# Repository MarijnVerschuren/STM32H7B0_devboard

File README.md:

# STM32H7B0_devboard
devboard featuring the STM32H7B0VBT6

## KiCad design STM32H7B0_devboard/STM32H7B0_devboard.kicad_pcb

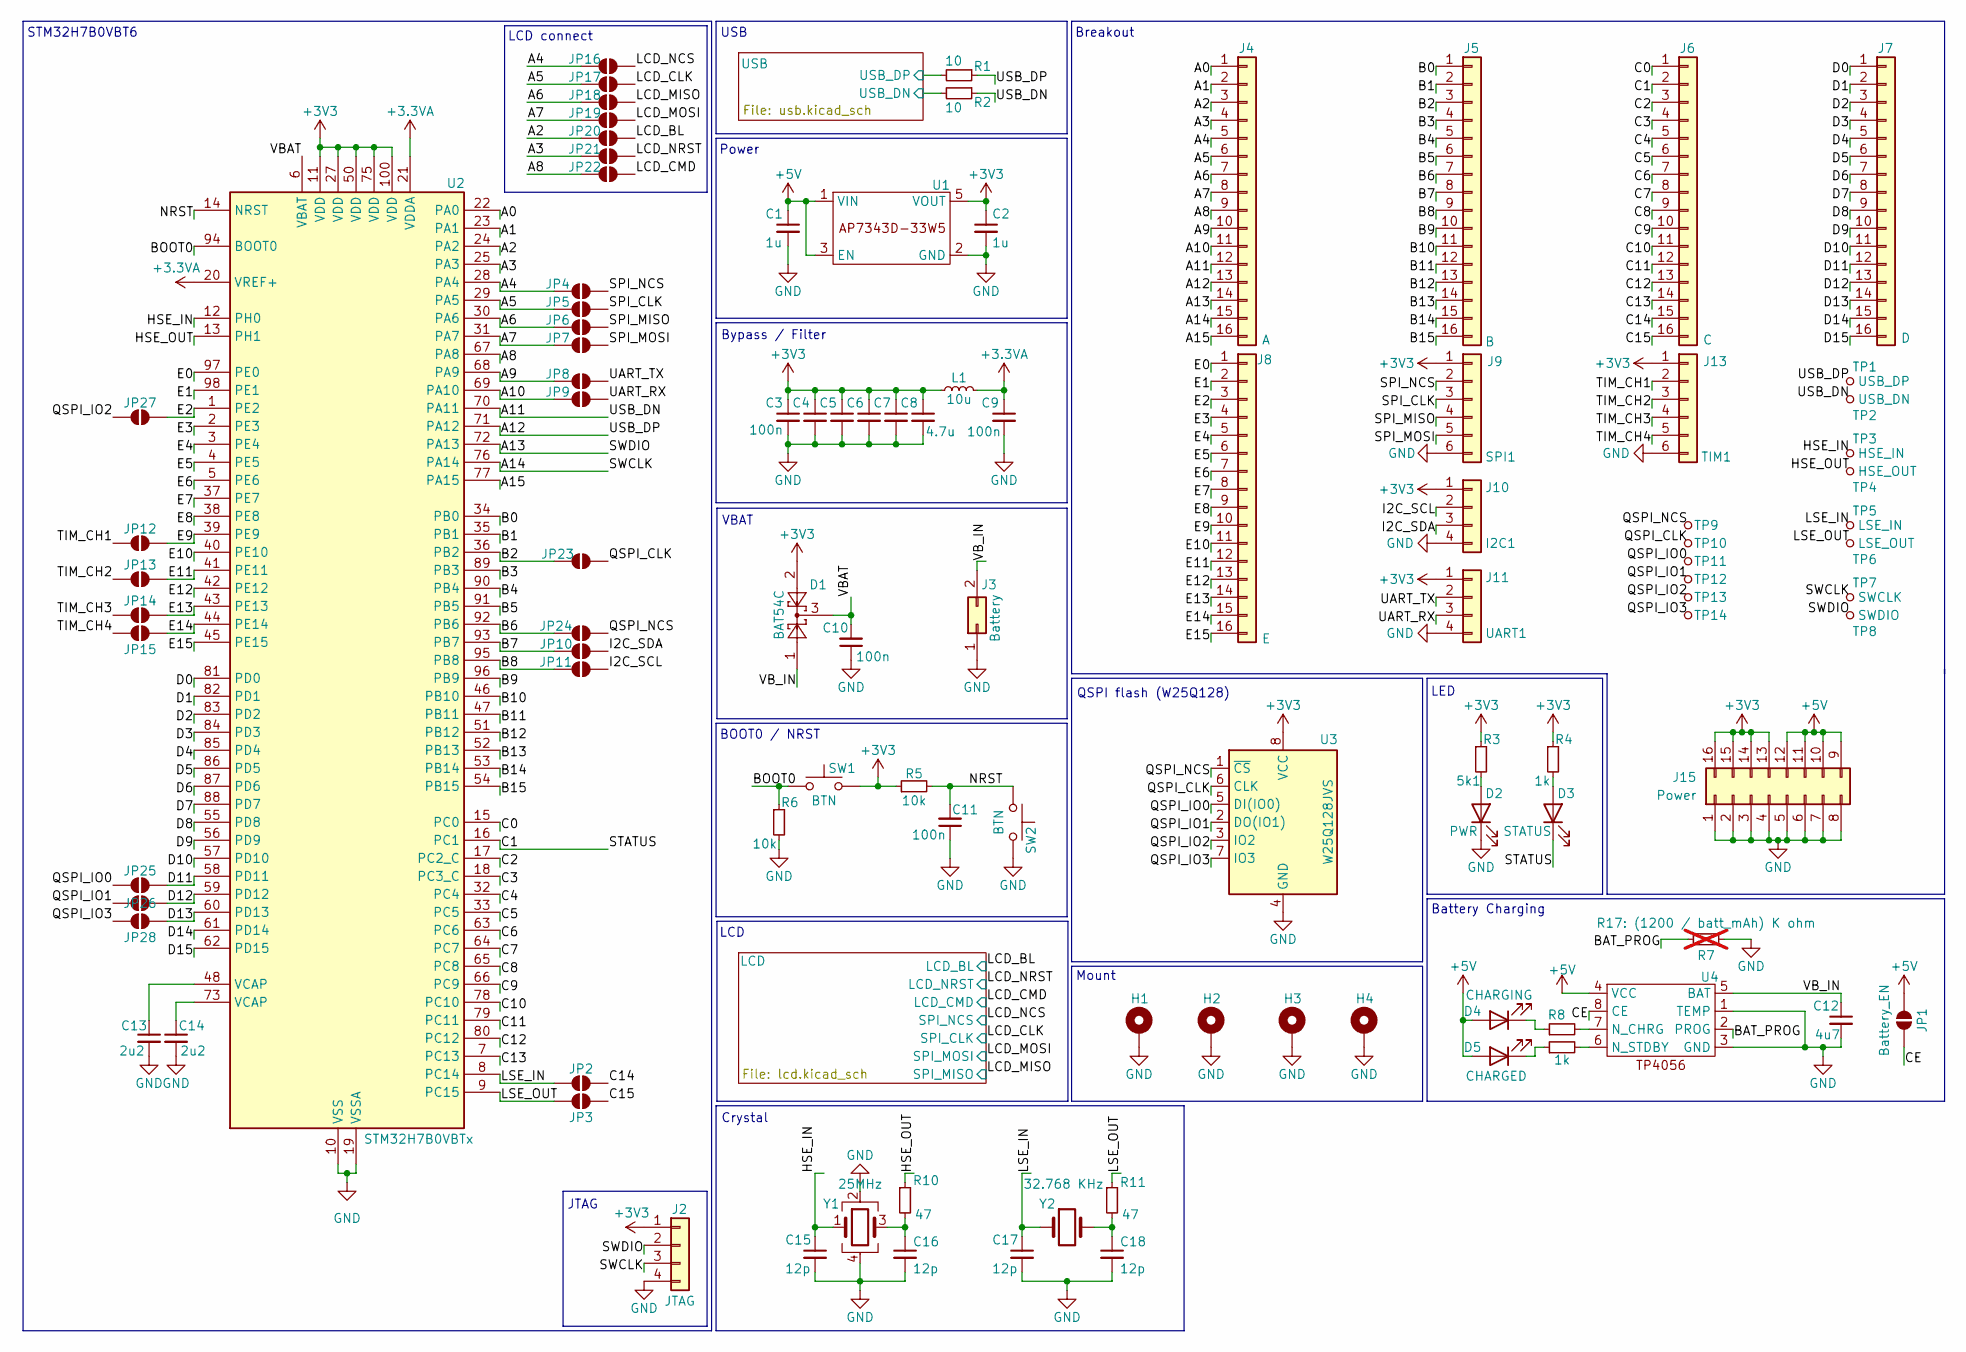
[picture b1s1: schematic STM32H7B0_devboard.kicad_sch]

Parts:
C1, C2: 1u; C_0603_1608Metric
C3, C4, C5, C6, C7, C9, C10, C11: 100n; C_0603_1608Metric
C8: 4.7u; C_0603_1608Metric
C12: 4u7; C_0603_1608Metric
C13, C14: 2u2; C_0402_1005Metric; LCSC C12530
C15, C16, C17, C18: 12p; C_0402_1005Metric; LCSC C1547
D1: BAT54C; SOT-23
D2: PWR; LED_0201_0603Metric
D3: STATUS; LED_0201_0603Metric
D4: CHARGING; LED_0603_1608Metric
D5: CHARGED; LED_0603_1608Metric
H1, H2, H3, H4: MountingHole_Pad; MountingHole_3.2mm_M3_Pad_Via
J2: JTAG; PinHeader_1x04_P2.00mm_Vertical
J3: Battery; PinHeader_1x02_P2.00mm_Vertical
J4: A; PinHeader_1x16_P2.00mm_Vertical
J5: B; PinHeader_1x16_P2.00mm_Vertical
J6: C; PinHeader_1x16_P2.00mm_Vertical
J7: D; PinHeader_1x16_P2.00mm_Vertical
J8: E; PinHeader_1x16_P2.00mm_Vertical
J9: SPI1; PinHeader_1x06_P2.00mm_Vertical
J10: I2C1; PinHeader_1x04_P2.00mm_Vertical
J11: UART1; PinHeader_1x04_P2.00mm_Vertical
J13: TIM1; PinHeader_1x06_P2.00mm_Vertical
J15: Power; PinHeader_2x08_P2.00mm_Vertical
JP1: Battery_EN; SolderJumper-2_P1.3mm_Open_TrianglePad1.0x1.5mm
JP2, JP3, JP4, JP5, JP6, JP7, JP8, JP9, JP10, JP11, JP12, JP13, JP14, JP15, JP16, JP17, JP18, JP19, JP20, JP21, JP22, JP23, JP24, JP25, JP26, JP27, JP28: SolderJumper_2_Open; SolderJumper-2_P1.3mm_Open_TrianglePad1.0x1.5mm
L1: 10u; L_0805_2012Metric
R1, R2: 10; R_0603_1608Metric
R3: 5k1; R_0603_1608Metric
R4, R8, R9: 1k; R_0603_1608Metric
R5, R6: 10k; R_0603_1608Metric
R7: R17: (1200 / batt_mAh) K ohm; R_0603_1608Metric; not fitted
R10, R11: 47; R_0603_1608Metric; LCSC C25118
SW1, SW2: BTN; SW_SPST_PTS810
TP1: USB_DP; TestPoint_THTPad_D1.0mm_Drill0.5mm
TP2: USB_DN; TestPoint_THTPad_D1.0mm_Drill0.5mm
TP3: HSE_IN; TestPoint_THTPad_D1.0mm_Drill0.5mm
TP4: HSE_OUT; TestPoint_THTPad_D1.0mm_Drill0.5mm
TP5: LSE_IN; TestPoint_THTPad_D1.0mm_Drill0.5mm
TP6: LSE_OUT; TestPoint_THTPad_D1.0mm_Drill0.5mm
TP7: SWCLK; TestPoint_THTPad_D1.0mm_Drill0.5mm
TP8: SWDIO; TestPoint_THTPad_D1.0mm_Drill0.5mm
TP9: QSPI_NCS; TestPoint_THTPad_D1.0mm_Drill0.5mm
TP10: QSPI_CLK; TestPoint_THTPad_D1.0mm_Drill0.5mm
TP11: QSPI_IO0; TestPoint_THTPad_D1.0mm_Drill0.5mm
TP12: QSPI_IO1; TestPoint_THTPad_D1.0mm_Drill0.5mm
TP13: QSPI_IO2; TestPoint_THTPad_D1.0mm_Drill0.5mm
TP14: QSPI_IO3; TestPoint_THTPad_D1.0mm_Drill0.5mm
U1: SOT-25
U2: STM32H7B0VBTx; LQFP-100_14x14mm_P0.5mm
U3: W25Q128JVS; SOIC-8_5.23x5.23mm_P1.27mm
U4: MSOP-8_3x3mm_P0.65mm
Y1: 25MHz; Crystal_SMD_3225-4Pin_3.2x2.5mm; LCSC C9006
Y2: 32.768 KHz; Crystal_SMD_3215-2Pin_3.2x1.5mm; LCSC C32346

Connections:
+3.3VA: C9.1, L1.2, U2.20 (VREF+), U2.21 (VDDA)
+3V3: C2.1, C3.1, C4.1, C5.1, C6.1, C7.1, C8.1, D1.2, J2.1, J9.1, J10.1, J11.1, J13.1, J15.13, J15.14, J15.15, J15.16, L1.1, R3.1, R4.1, R5.1, SW1.2, U1.5 (VOUT), U2.11 (VDD), U2.27 (VDD), U2.50 (VDD), U2.75 (VDD), U2.100 (VDD), U3.8 (VCC); also elsewhere on the board
+5V: C1.1, D4.2 (A), D5.2 (A), J15.9, J15.10, J15.11, J15.12, JP1.1 (A), U1.1 (VIN), U1.3 (EN), U4.4 (VCC); also elsewhere on the board
/A0: J4.1, U2.22 (PA0)
/A1: J4.2, U2.23 (PA1)
/A2: J4.3, JP20.1 (A), U2.24 (PA2)
/A3: J4.4, JP21.1 (A), U2.25 (PA3)
/A4: J4.5, JP4.1 (A), JP16.1 (A), U2.28 (PA4)
/A5: J4.6, JP5.1 (A), JP17.1 (A), U2.29 (PA5)
/A6: J4.7, JP6.1 (A), JP18.1 (A), U2.30 (PA6)
/A7: J4.8, JP7.1 (A), JP19.1 (A), U2.31 (PA7)
/A8: J4.9, JP22.1 (A), U2.67 (PA8)
/A9: J4.10, JP8.1 (A), U2.68 (PA9)
/A10: J4.11, JP9.1 (A), U2.69 (PA10)
/A11: J4.12, R2.1, TP2.1, U2.70 (PA11)
/A12: J4.13, R1.1, TP1.1, U2.71 (PA12)
/A13: J2.2, J4.14, TP8.1, U2.72 (PA13)
/A14: J2.3, J4.15, TP7.1, U2.76 (PA14)
/A15: J4.16, U2.77 (PA15)
/B0: J5.1, U2.34 (PB0)
/B1: J5.2, U2.35 (PB1)
/B2: J5.3, JP23.1 (A), U2.36 (PB2)
/B3: J5.4, U2.89 (PB3)
/B4: J5.5, U2.90 (PB4)
/B5: J5.6, U2.91 (PB5)
/B6: J5.7, JP24.1 (A), U2.92 (PB6)
/B7: J5.8, JP10.1 (A), U2.93 (PB7)
/B8: J5.9, JP11.1 (A), U2.95 (PB8)
/B9: J5.10, U2.96 (PB9)
/B10: J5.11, U2.46 (PB10)
/B11: J5.12, U2.47 (PB11)
/B12: J5.13, U2.51 (PB12)
/B13: J5.14, U2.52 (PB13)
/B14: J5.15, U2.53 (PB14)
/B15: J5.16, U2.54 (PB15)
/BAT_PROG: R7.1, U4.2 (PROG)
/BOOT0: R6.1, SW1.1, U2.94 (BOOT0)
/C0: J6.1, U2.15 (PC0)
/C1: D3.1 (K), J6.2, U2.16 (PC1)
/C2: J6.3, U2.17 (PC2_C)
/C3: J6.4, U2.18 (PC3_C)
/C4: J6.5, U2.32 (PC4)
/C5: J6.6, U2.33 (PC5)
/C6: J6.7, U2.63 (PC6)
/C7: J6.8, U2.64 (PC7)
/C8: J6.9, U2.65 (PC8)
/C9: J6.10, U2.66 (PC9)
/C10: J6.11, U2.78 (PC10)
/C11: J6.12, U2.79 (PC11)
/C12: J6.13, U2.80 (PC12)
/C13: J6.14, U2.7 (PC13)
/C14: J6.15, JP2.2 (B)
/C15: J6.16, JP3.2 (B)
/CE: JP1.2 (B), U4.8 (CE)
/D0: J7.1, U2.81 (PD0)
/D1: J7.2, U2.82 (PD1)
/D2: J7.3, U2.83 (PD2)
/D3: J7.4, U2.84 (PD3)
/D4: J7.5, U2.85 (PD4)
/D5: J7.6, U2.86 (PD5)
/D6: J7.7, U2.87 (PD6)
/D7: J7.8, U2.88 (PD7)
/D8: J7.9, U2.55 (PD8)
/D9: J7.10, U2.56 (PD9)
/D10: J7.11, U2.57 (PD10)
/D11: J7.12, JP25.2 (B), U2.58 (PD11)
/D12: J7.13, JP26.2 (B), U2.59 (PD12)
/D13: J7.14, JP28.2 (B), U2.60 (PD13)
/D14: J7.15, U2.61 (PD14)
/D15: J7.16, U2.62 (PD15)
/E0: J8.1, U2.97 (PE0)
/E1: J8.2, U2.98 (PE1)
/E2: J8.3, JP27.2 (B), U2.1 (PE2)
/E3: J8.4, U2.2 (PE3)
/E4: J8.5, U2.3 (PE4)
/E5: J8.6, U2.4 (PE5)
/E6: J8.7, U2.5 (PE6)
/E7: J8.8, U2.37 (PE7)
/E8: J8.9, U2.38 (PE8)
/E9: J8.10, JP12.2 (B), U2.39 (PE9)
/E10: J8.11, U2.40 (PE10)
/E11: J8.12, JP13.2 (B), U2.41 (PE11)
/E12: J8.13, U2.42 (PE12)
/E13: J8.14, JP14.2 (B), U2.43 (PE13)
/E14: J8.15, JP15.2 (B), U2.44 (PE14)
/E15: J8.16, U2.45 (PE15)
/HSE_IN: C15.1, TP3.1, U2.12 (PH0), Y1.1
/HSE_OUT: R10.1, TP4.1, U2.13 (PH1)
/I2C_SCL: J10.2, JP11.2 (B)
/I2C_SDA: J10.3, JP10.2 (B)
/LCD_BL: JP20.2 (B); also elsewhere on the board
/LCD_CLK: JP17.2 (B); also elsewhere on the board
/LCD_CMD: JP22.2 (B); also elsewhere on the board
/LCD_MISO: JP18.2 (B); also elsewhere on the board
/LCD_MOSI: JP19.2 (B); also elsewhere on the board
/LCD_NCS: JP16.2 (B); also elsewhere on the board
/LCD_NRST: JP21.2 (B); also elsewhere on the board
/LSE_IN: C17.1, JP2.1 (A), TP5.1, U2.8 (PC14), Y2.1
/LSE_OUT: JP3.1 (A), R11.1, TP6.1, U2.9 (PC15)
/NRST: C11.2, R5.2, SW2.1, U2.14 (NRST)
/QSPI_CLK: JP23.2 (B), TP10.1, U3.6 (CLK)
/QSPI_IO0: JP25.1 (A), TP11.1, U3.5 (DI(IO0))
/QSPI_IO1: JP26.1 (A), TP12.1, U3.2 (DO(IO1))
/QSPI_IO2: JP27.1 (A), TP13.1, U3.3 (IO2)
/QSPI_IO3: JP28.1 (A), TP14.1, U3.7 (IO3)
/QSPI_NCS: JP24.2 (B), TP9.1, U3.1 (~CS)
/SPI_CLK: J9.3, JP5.2 (B)
/SPI_MISO: J9.4, JP6.2 (B)
/SPI_MOSI: J9.5, JP7.2 (B)
/SPI_NCS: J9.2, JP4.2 (B)
/TIM_CH1: J13.2, JP12.1 (A)
/TIM_CH2: J13.3, JP13.1 (A)
/TIM_CH3: J13.4, JP14.1 (A)
/TIM_CH4: J13.5, JP15.1 (A)
/UART_RX: J11.3, JP9.2 (B)
/UART_TX: J11.2, JP8.2 (B)
/USB/USB_DN: R2.2; also elsewhere on the board
/USB/USB_DP: R1.2; also elsewhere on the board
/VBAT: C10.2, D1.3, U2.6 (VBAT)
/VB_IN: C12.1, D1.1, J3.2, U4.5 (BAT)
GND: C1.2, C2.2, C3.2, C4.2, C5.2, C6.2, C7.2, C8.2, C9.2, C10.1, C11.1, C12.2, C13.2, C14.2, C15.2, C16.2, C17.2, C18.2, D2.1 (K), H1.1, H2.1, H3.1, H4.1, J2.4, J3.1, J9.6, J10.4, J11.4, J13.6, J15.1, J15.2, J15.3, J15.4, J15.5, J15.6, J15.7, J15.8, R6.2, R7.2, SW2.2, U1.2 (GND), U2.10 (VSS), U2.19 (VSSA), U2.26 (VSS), U2.49 (VSS), U2.74 (VSS), U2.99 (VSS), U3.4 (GND), U4.1 (TEMP), U4.3 (GND), Y1.2, Y1.4; also elsewhere on the board
unnamed: C13.1, U2.48 (VCAP)
unnamed: C14.1, U2.73 (VCAP)
unnamed: C16.1, R10.2, Y1.3
unnamed: C18.1, R11.2, Y2.2
unnamed: D2.2 (A), R3.2
unnamed: D3.2 (A), R4.2
unnamed: D4.1 (K), R8.1
unnamed: D5.1 (K), R9.1
unnamed: R8.2, U4.7 (N_CHRG)
unnamed: R9.2, U4.6 (N_STDBY)

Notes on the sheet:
Battery Charging
Power
LCD
LCD connect
VBAT
QSPI flash (W25Q128)
LED
BOOT0 / NRST
JTAG
USB
STM32H7B0VBT6
Crystal
Bypass / Filter
Mount
Breakout

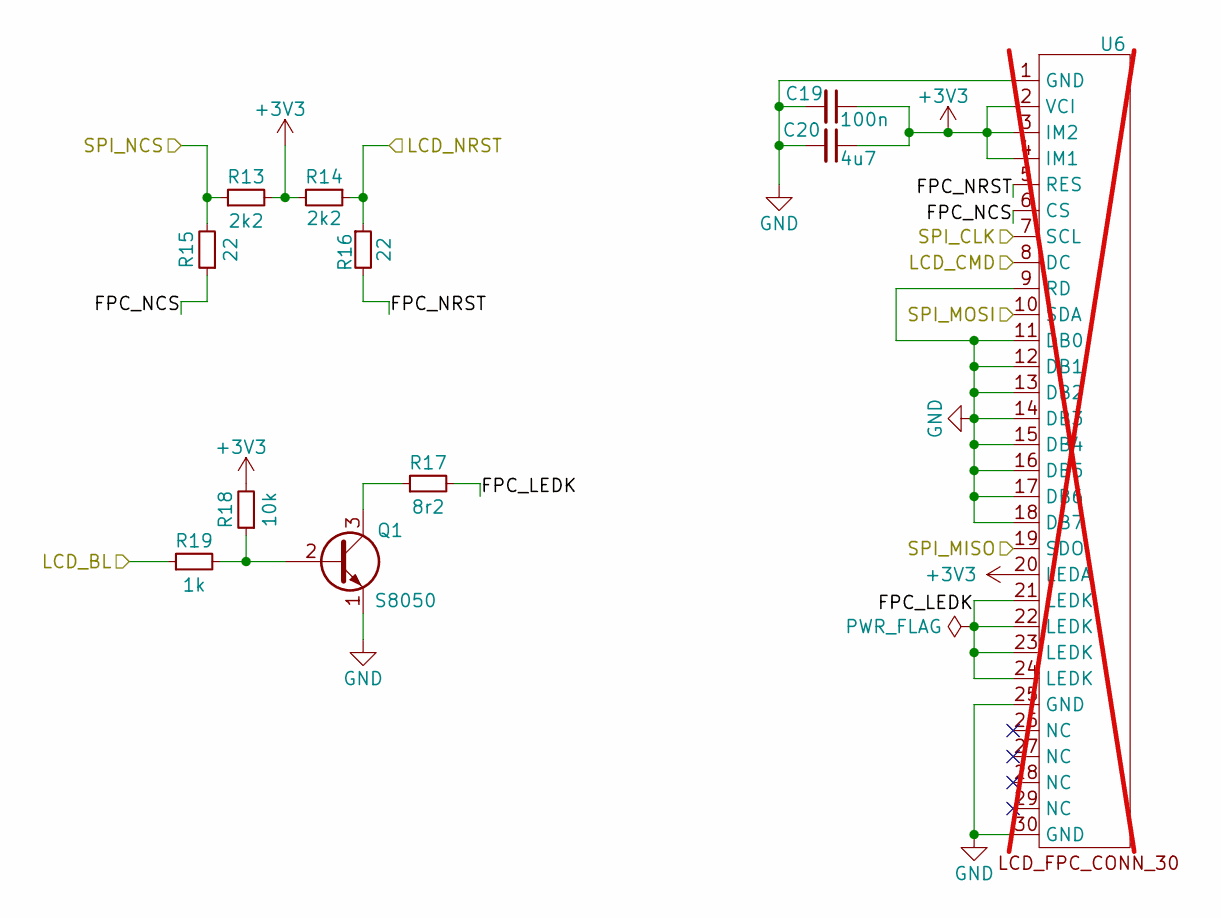
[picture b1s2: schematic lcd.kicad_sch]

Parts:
C19: 100n; C_0402_1005Metric; LCSC C1525
C20: 4u7; C_0402_1005Metric; LCSC C23733
Q1: S8050; SOT-23; LCSC C2146
R13, R14: 2k2; R_0603_1608Metric; LCSC C25879
R15, R16: 22; R_0603_1608Metric; LCSC C25092
R17: 8r2; R_0603_1608Metric; LCSC C2849042
R18: 10k; R_0603_1608Metric; LCSC C25744
R19: 1k; R_0603_1608Metric; LCSC C11702
U6: FPC_30_soldered; not fitted

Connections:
+3V3: C19.1, C20.1, R13.2, R14.2, R18.2, U6.2 (VCI), U6.3 (IM2), U6.4 (IM1), U6.20 (LEDA); also elsewhere on the board
/LCD/FPC_LEDK: R17.2, U6.21 (LEDK), U6.22 (LEDK), U6.23 (LEDK), U6.24 (LEDK)
/LCD/FPC_NCS: R15.1, U6.6 (CS)
/LCD/FPC_NRST: R16.2, U6.5 (RES)
/LCD_BL: R19.1; also elsewhere on the board
/LCD_CLK: U6.7 (SCL); also elsewhere on the board
/LCD_CMD: U6.8 (DC); also elsewhere on the board
/LCD_MISO: U6.19 (SDO); also elsewhere on the board
/LCD_MOSI: U6.10 (SDA); also elsewhere on the board
/LCD_NCS: R13.1, R15.2; also elsewhere on the board
/LCD_NRST: R14.1, R16.1; also elsewhere on the board
GND: C19.2, C20.2, Q1.1 (E), U6.1 (GND), U6.9 (RD), U6.11 (DB0), U6.12 (DB1), U6.13 (DB2), U6.14 (DB3), U6.15 (DB4), U6.16 (DB5), U6.17 (DB6), U6.18 (DB7), U6.25 (GND), U6.30 (GND); also elsewhere on the board
unnamed: Q1.2 (B), R18.1, R19.2
unnamed: Q1.3 (C), R17.1

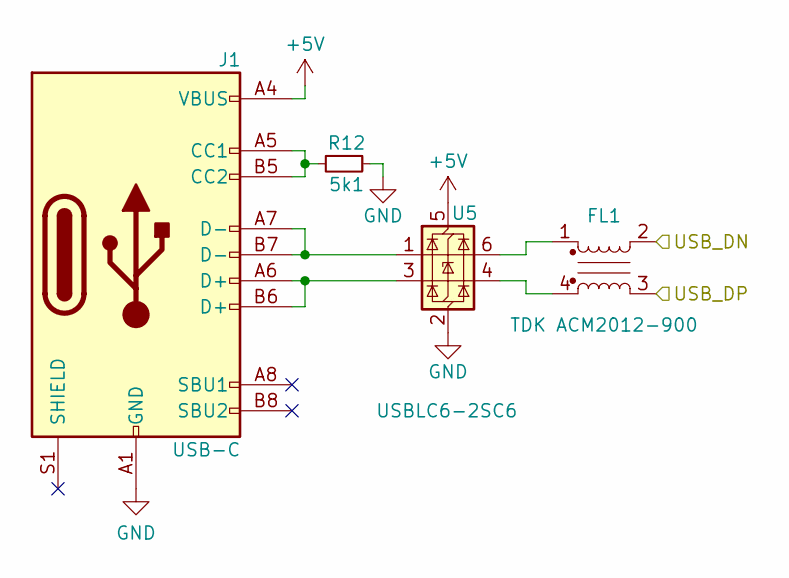
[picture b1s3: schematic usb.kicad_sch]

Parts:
FL1: TDK ACM2012-900; ACM2012_TDK; LCSC C19972
J1: USB-C; USB_C_Receptacle_G-Switch_GT-USB-7010ASV
R12: 5k1; R_0603_1608Metric; LCSC C23186
U5: USBLC6-2SC6; SOT-23-6; LCSC C2827654

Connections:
+5V: J1.A4 (VBUS), J1.A9 (VBUS), J1.B4 (VBUS), J1.B9 (VBUS), U5.5 (VBUS); also elsewhere on the board
/USB/USB_DN: FL1.2; also elsewhere on the board
/USB/USB_DP: FL1.3; also elsewhere on the board
GND: J1.A1 (GND), J1.A12 (GND), J1.B1 (GND), J1.B12 (GND), R12.1, U5.2 (GND); also elsewhere on the board
unnamed: FL1.1, U5.6 (I/O1)
unnamed: FL1.4, U5.4 (I/O2)
unnamed: J1.A5 (CC1), J1.B5 (CC2), R12.2
unnamed: J1.A6 (D+), J1.B6 (D+), U5.3 (I/O2)
unnamed: J1.A7 (D-), J1.B7 (D-), U5.1 (I/O1)

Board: 2 copper layers, 116 parts (0 on the bottom side), 141 nets, no tracks yet.

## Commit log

2024-01-26 Created project
2024-04-19 Created KiCad project
2024-04-21 Schematic V0
2024-04-22 Schematic V0.1
2024-04-22 Schematic V0.2
2024-04-22 Added TODOs
2024-04-25 Schematic V1.0
2024-04-25 Sorted schematic components
2024-04-25 Added .gitignore
2024-04-26 Schematic done!
2024-05-11 Breakout
2024-05-11 Schematic V2.0 + Footprints
2024-05-12 Updated .gitignore
2024-05-12 Started on layout
2024-05-13 Constraints
2024-05-13 Layout V2
2024-05-14 Buck
2024-05-14 Routing progress
2024-05-14 Routing process
2024-05-14 Routing done!
2024-05-14 Silk screen progress
2024-05-15 Done V1
2024-05-15 Done V1.1
2024-05-15 Pin labels
2024-05-16 Manufacturer switch
2024-05-18 Finished board
2024-05-23 Copper balance
2024-05-25 Started on V2
2024-06-15 Upgraded QSPI flash
2024-06-16 Schematic complete
